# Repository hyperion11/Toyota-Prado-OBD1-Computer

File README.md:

# Toyota-Prado-OBD1-Computer
OBD1 Car computer for Toyota land Cruiser Prado 90 95 1997-2002 5VZ-FE or 3RZ-FE engine

For "Thanks!" you can give me a "coffee" :)

https://www.tinkoff.ru/rm/degtyarev.aleksey35/kHApi80257

or

https://paypal.me/alekseydegtyarev1986?locale.x=ru_RU

BILL OF MATERIALS:

Maple Mini STM32 Dev board http://alii.pub/5snybc

2.4' ILI9341 SPI TFT Screen with flex cable w\o touch http://alii.pub/5snyhd

Capacitors:
22uF 0805 5pcs
http://alii.pub/5snzpw

1uF 0805 2pcs
http://alii.pub/5snzpw

0.1uF 0805 7pcs
http://alii.pub/5snzpw

3.3nF 0805 1pcs
http://alii.pub/5snzpw

100uF 0805 1pcs
http://alii.pub/5snzvc

Diode DO214
http://alii.pub/5so00s

ADC    B4B-ZRROUND           B4B-ZRROUND            B4B-ZR                JST-ZH Connector                                                                                       

BT2                          BATTERY                BATTCOM_20MM_VERTICAL Battery - Single Cell                                                                                 

PTC Fuse 1206 0.7-1A
http://alii.pub/5so034
 
FRAM MB85RC04VPNF 3.3v
http://alii.pub/5so077

LN6206                       MCP1700                SOT23                                                                                                                     LN6206P302MR-G                                                                                                                                                                                                      
Q1     PDTC143XT             MUN2211T1              SC59-BEC              NPN Bias Resistor Transistor                                                                                                                0                                                                                                                                                                           
Q2     PDTA143ZT             MUN2111T1              SC59-BEC              PNP Bias Resistor Transistor                                                                                                                0                                                                                                                                                                           
R1     33K                   R-EU_R0805             R0805                 RESISTOR, European symbol                                                                                                                                                                                                                                                                                               
R3     4                     R-EU_R0805             R0805                 RESISTOR, European symbol                                                                                                                                                                                                                                                                                               
R4     PHOTORESPDV-P9        PHOTORESPDV-P9         PDV-P9XXX             Photoresistor                                                                                                                                                                                                                                                                                                           
R10    20K                   R-EU_R0805             R0805                 RESISTOR, European symbol                                                                                                                                                                                                                                                                                               
R11    6.8K                  R-EU_R0805             R0805                 RESISTOR, European symbol                                                                                                                                                                                                                                                                                               
R12    3.3K                  R-EU_R0805             R0805                 RESISTOR, European symbol                                                                                                                                                                                                                                                                                               
R13    10K                   R-EU_R0805             R0805                 RESISTOR, European symbol                                                                                                                                                                                                                                                                                               
R31    4.7K                  R-EU_R0805             R0805                 RESISTOR, European symbol                                                                                                                                                                                                                                                                                               
R32    4.7K                  R-EU_R0805             R0805                 RESISTOR, European symbol                                                                                                                                                                                                                                                                                               
R38    100                   R-EU_R0805             R0805                 RESISTOR, European symbol                                                                                                                                                                                                                                                                                               
RN1    10K                   RN2_EU-4               CTS-744*083           Chip Resistor Array's from various manufactures                                                     CRA064RJ10K0E04Z                                                                                                                                                                                                    
RN2    2.2K                  RN2_EU-4               CTS-744*083           Chip Resistor Array's from various manufactures                                                     CRA064RJ10K0E04Z                                                                                                                                                                                                    
RN3    10K                   RN2_EU-4               CTS-744*083           Chip Resistor Array's from various manufactures                                                     CRA064RJ10K0E04Z                                                                                                                                                                                                    
RN4    2.2K                  RN2_EU-4               CTS-744*083           Chip Resistor Array's from various manufactures                                                     CRA064RJ10K0E04Z                                                                                                                                                                                                    
S1     DTSM-6                DTSM-6                 DTSM-6                                                                                                                                                                                                                                                                                                                                        
S2     DTSM-6                DTSM-6                 DTSM-6                                                                                                                                                                                                                                                                                                                                        
S3     DTSM-6                DTSM-6                 DTSM-6                                                                                                                                                                                                                                                                                                                                        
S4     DTSM-6                DTSM-6                 DTSM-6                                                                                                                                                                                                                                                                                                                                        
S5     DTSM-6                DTSM-6                 DTSM-6                                                                                                                                                                                                                                                                                                                                        
SERIAL B4B-ZRROUND           B4B-ZRROUND            B4B-ZR                JST-ZH Connector                                                                                                                                                                                                                                                                                                        
SG2    F/QMBIII              F/QMBIII               F/QMBIII              BUZZER Source: Buerklin                                                                                                unknown    unknown   1                                                                                                                                                                                                                                                                                                                          
U$2    JUSHUOAFC08-S18FCA-00 JUSHUOAFC08-S18FCA-00  JUSHUOAFC08-S18FCA-00                                                                                                     AFC08-S18FCA-00                                                                                                                                                                                                     
U$3    main                  B5B-ZRLONG             B5B-ZR-LONG           JST-ZH Connector                                                                                                                                                                                                                                                                                                        
U$4    MINI-DC-DC-3AV        MINI-DC-DC-3AV         MINI-DC-DC-3AV                                                                                                                                                                                                                                                                                                                                
U$5    ADC-4CH-ADS1115       ADC-4CH-ADS1115        ADC-4CH-ADS1115       4 Channel 16-Bit Analog-to-Digital Converter based on ADS1115 chip

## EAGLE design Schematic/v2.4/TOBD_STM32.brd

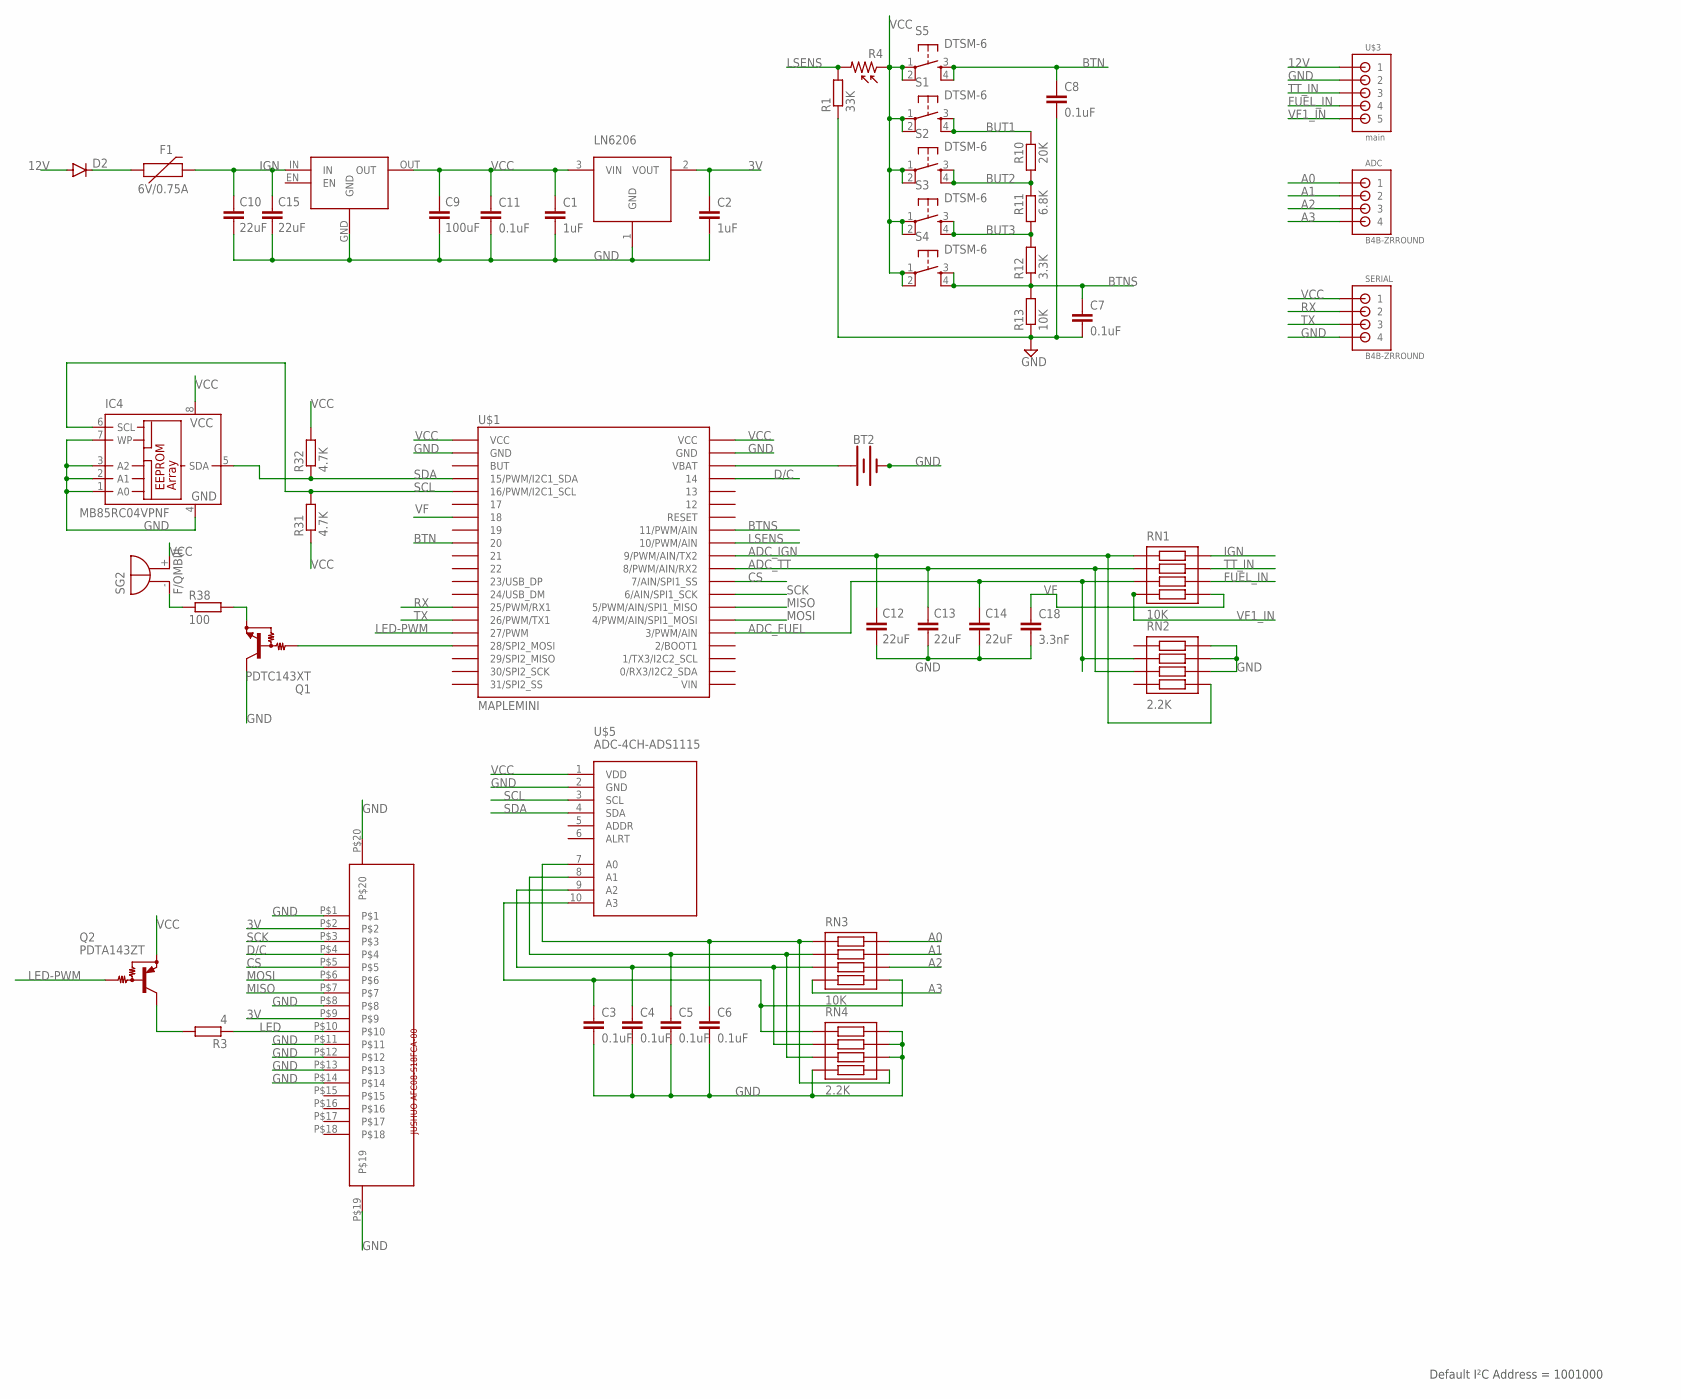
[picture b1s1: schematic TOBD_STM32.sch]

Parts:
ADC: B4B-ZRROUND; B4B-ZR
BT2: BATTERY; BATTCOM_20MM_VERTICAL
C1, C2: 1uF; C0805; MPN CL21F105ZOFNNNE
C3, C4, C5, C6, C7, C8, C11: 0.1uF; C0805; MPN CL21F104ZBCNNNC
C9: 100uF; C1210K; MPN GRM32ER60J107ME20L; LCSC C88154
C10, C12, C13, C14, C15: 22uF; C0805; MPN CL21A226MAQNNNE; LCSC C45783
C18: 3.3nF; C0805; MPN CL21B332KBANNNC
D2: DIODE-DO-214AC; DO-214AC
F1: 6V/0.75A; 1206
IC4: MB85RC04VPNF; SO-08
LN6206: MCP1700; SOT23; MPN LN6206P302MR-G
Q1: PDTC143XT; SC59-BEC
Q2: PDTA143ZT; SC59-BEC
R1: 33K; R0805
R3: 4; R0805
R4: PHOTORESPDV-P9; PDV-P9XXX
R10: 20K; R0805
R11: 6.8K; R0805
R12: 3.3K; R0805
R13: 10K; R0805
R31, R32: 4.7K; R0805
R38: 100; R0805
RN1, RN3: 10K; CTS-744*083; MPN CRA064RJ10K0E04Z
RN2, RN4: 2.2K; CTS-744*083; MPN CRA064RJ10K0E04Z
S1, S2, S3, S4, S5: DTSM-6
SERIAL: B4B-ZRROUND; B4B-ZR
SG2: F/QMBIII
U$1: MAPLEMINI; 20-DIP
U$2: JUSHUOAFC08-S18FCA-00; MPN AFC08-S18FCA-00
U$3: main; B5B-ZR-LONG
U$4: MINI-DC-DC-3AV
U$5: ADC-4CH-ADS1115

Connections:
3V: C2.1, LN6206.2 (VOUT), U$2.P$2, U$2.P$9
12V: D2.A, U$3.1
A0: ADC.1, RN3.5 (8)
A1: ADC.2, RN3.6 (7)
A2: ADC.3, RN3.7 (6)
A3: ADC.4, RN3.8 (4)
ADC_FUEL: C14.1, RN1.2 (3), RN2.3 (2), U$1.25 (3/PWM/AIN)
ADC_IGN: C12.1, RN1.4 (1), RN2.1 (5), U$1.31 (9/PWM/AIN/TX2)
ADC_TT: C13.1, RN1.3 (2), RN2.2 (3), U$1.30 (8/PWM/AIN/RX2)
BTN: C8.1, S5.3, S5.4, U$1.9 (20)
BTNS: C7.1, R12.1, R13.2, S4.3, S4.4, U$1.33 (11/PWM/AIN)
BUT1: R10.2, S1.3, S1.4
BUT2: R10.1, R11.2, S2.3, S2.4
BUT3: R11.1, R12.2, S3.3, S3.4
CS: U$1.29 (7/AIN/SPI1_SS), U$2.P$5
D/C: U$1.37 (14), U$2.P$4
FUEL_IN: RN1.7 (6), U$3.4
GND: BT2.3 (-), C1.2, C2.2, C3.2, C4.2, C5.2, C6.2, C7.2, C8.2, C9.2, C10.2, C11.2, C12.2, C13.2, C14.2, C15.2, C18.2, IC4.1 (A0), IC4.2 (A1), IC4.3 (A2), IC4.4 (GND), IC4.7 (WP), LN6206.1 (GND), Q1.C, R1.1, R13.1, RN2.5 (8), RN2.6 (7), RN2.7 (6), RN4.5 (8), RN4.6 (7), RN4.7 (6), RN4.8 (4), SERIAL.4, U$1.2 (GND), U$1.39 (GND), U$2.P$1, U$2.P$8, U$2.P$11, U$2.P$12, U$2.P$13, U$2.P$14, U$2.P$19, U$2.P$20, U$3.2, U$4.GND, U$5.2 (GND)
IGN: C10.1, C15.1, F1.2, RN1.5 (8), U$4.IN
LED: R3.1, U$2.P$10
LED-PWM: Q2.B, U$1.16 (27/PWM)
LSENS: R1.2, R4.2, U$1.32 (10/PWM/AIN)
MISO: U$1.27 (5/PWM/AIN/SPI1_MISO), U$2.P$7
MOSI: U$1.26 (4/PWM/AIN/SPI1_MOSI), U$2.P$6
unnamed: R38.1, SG2.- (+)
unnamed: Q2.C, R3.2
unnamed: D2.C, F1.1
unnamed: C6.1, RN3.4 (1), RN4.1 (5), U$5.7 (A0)
unnamed: C5.1, RN3.3 (2), RN4.2 (3), U$5.8 (A1)
unnamed: C4.1, RN3.2 (3), RN4.3 (2), U$5.9 (A2)
unnamed: C3.1, RN3.1 (5), RN4.4 (1), U$5.10 (A3)
unnamed: Q1.B, U$1.17 (28/SPI2_MOSI)
unnamed: Q1.E, R38.2
RX: SERIAL.2, U$1.14 (25/PWM/RX1)
SCK: U$1.28 (6/AIN/SPI1_SCK), U$2.P$3
SCL: IC4.6 (SCL), R31.2, U$1.5 (16/PWM/I2C1_SCL), U$5.3 (SCL)
SDA: IC4.5 (SDA), R32.1, U$1.4 (15/PWM/I2C1_SDA), U$5.4 (SDA)
TT_IN: RN1.6 (7), U$3.3
TX: SERIAL.3, U$1.15 (26/PWM/TX1)
VBAT1: BT2.1 (+), BT2.2 (+), U$1.38 (VBAT)
VCC: C1.1, C9.1, C11.1, IC4.8 (VCC), LN6206.3 (VIN), Q2.E, R4.1, R31.1, R32.2, S1.1, S1.2, S2.1, S2.2, S3.1, S3.2, S4.1, S4.2, S5.1, S5.2, SERIAL.1, SG2.+ (-), U$1.1 (VCC), U$1.40 (VCC), U$4.OUT, U$5.1 (VDD)
VF: C18.1, RN1.1 (5), U$1.7 (18)
VF1_IN: RN1.8 (4), U$3.5

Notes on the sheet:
Default I²C Address = 1001000

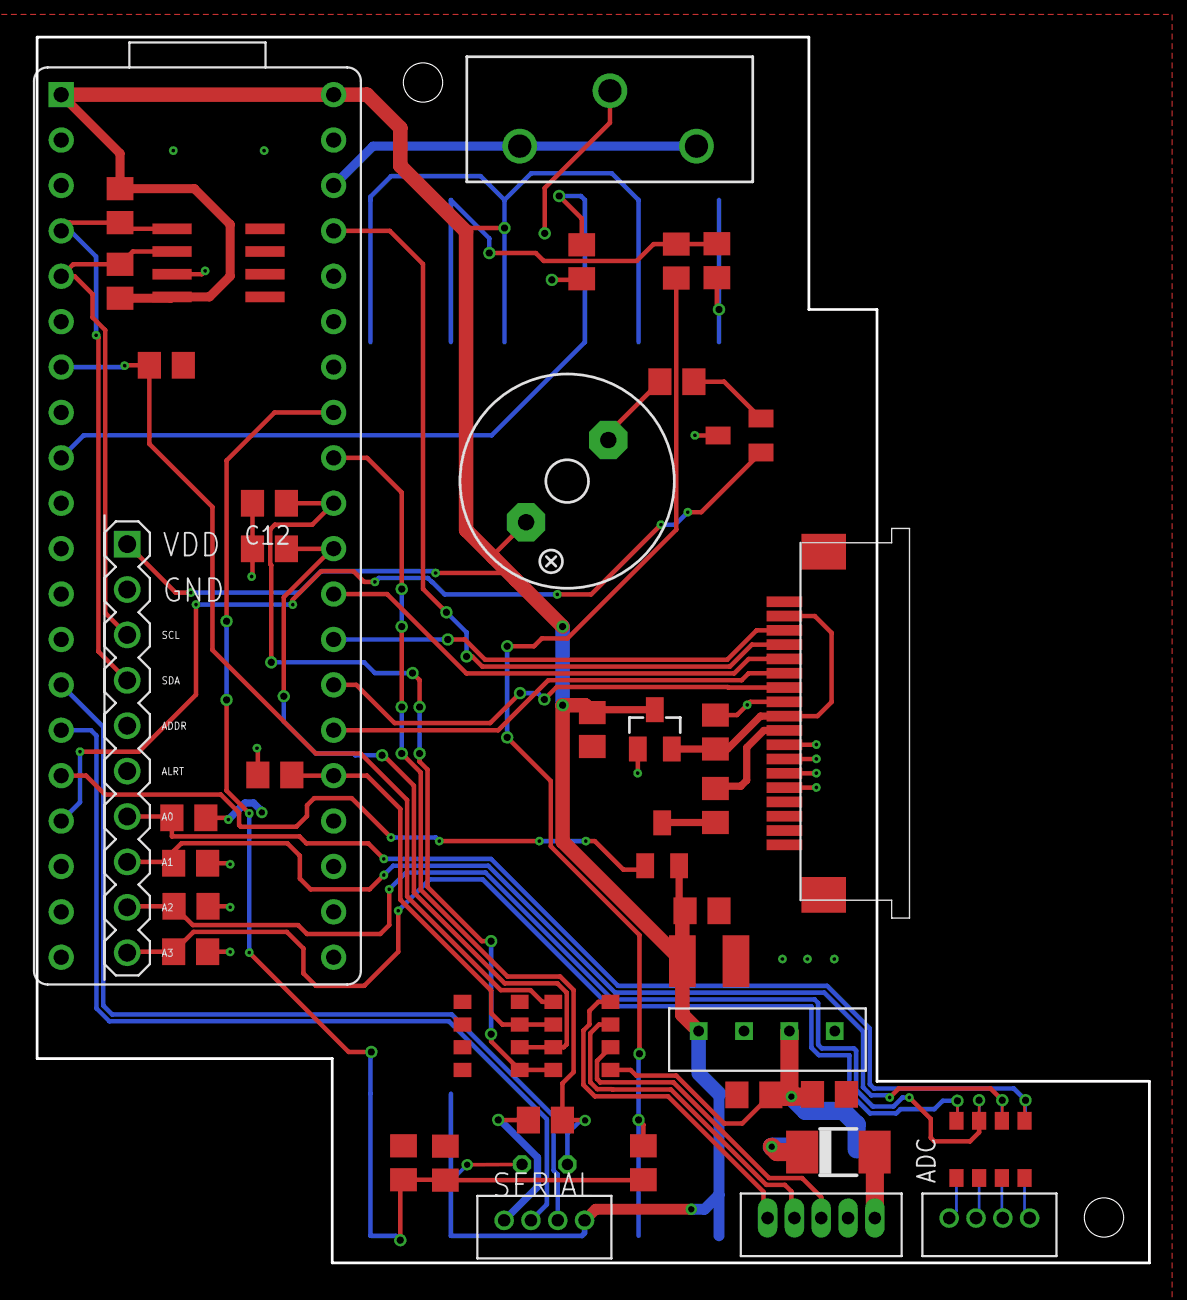
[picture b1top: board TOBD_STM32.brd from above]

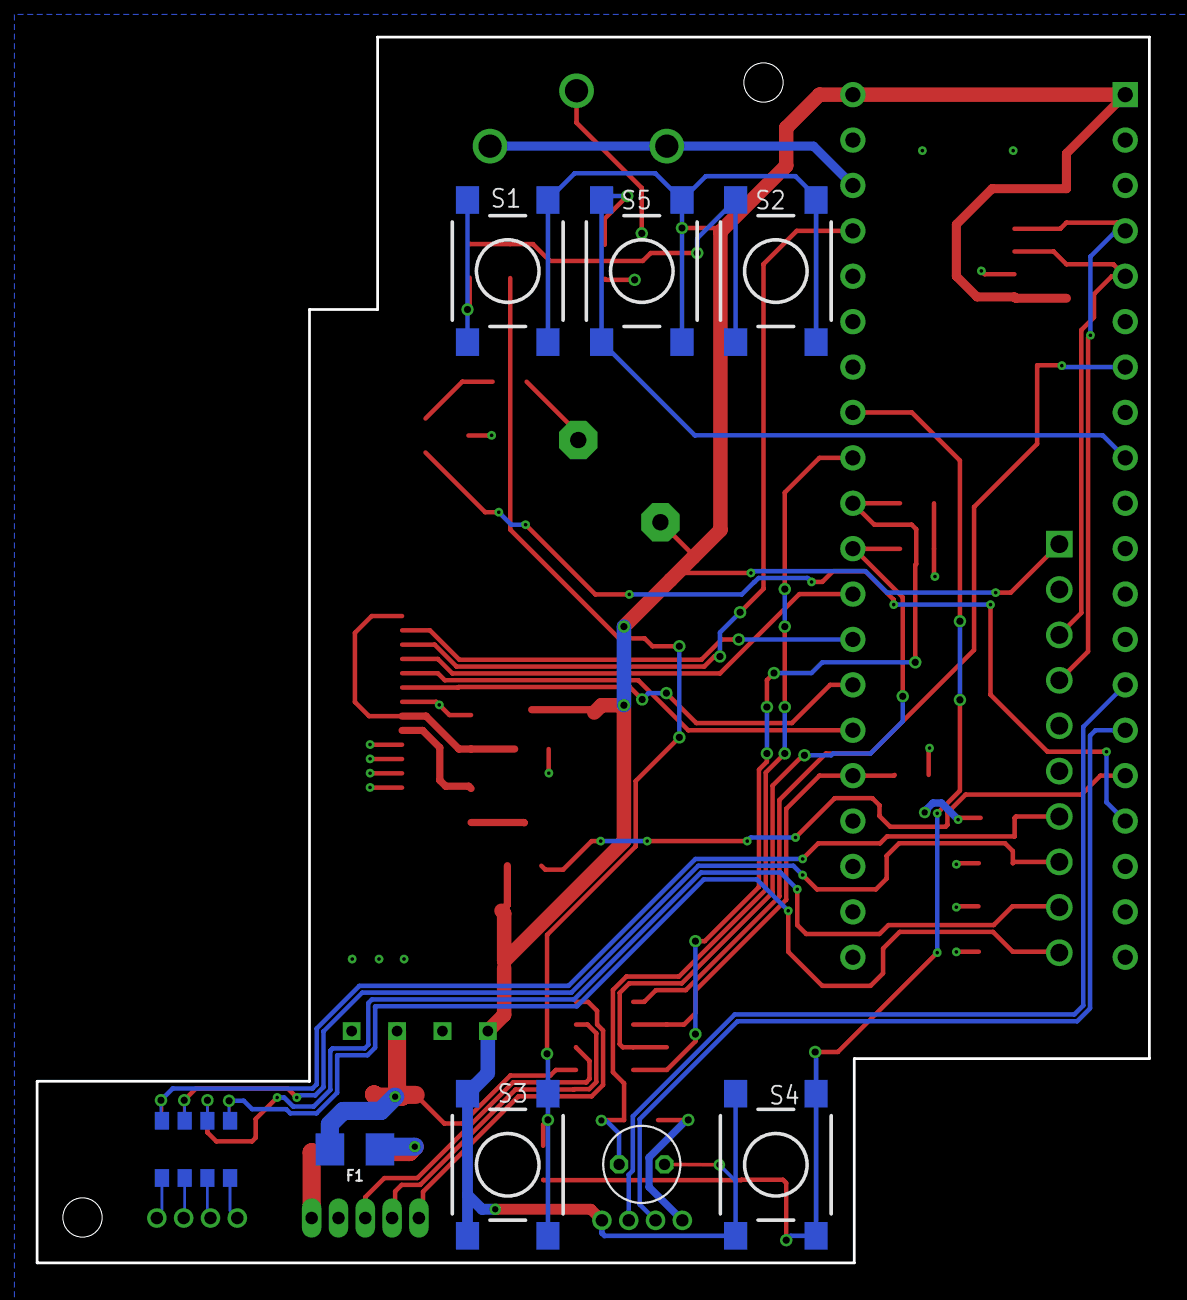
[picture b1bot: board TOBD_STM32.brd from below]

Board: 2 copper layers, 62.2 x 68.6 mm, 50 parts (8 on the bottom side), 43 nets.

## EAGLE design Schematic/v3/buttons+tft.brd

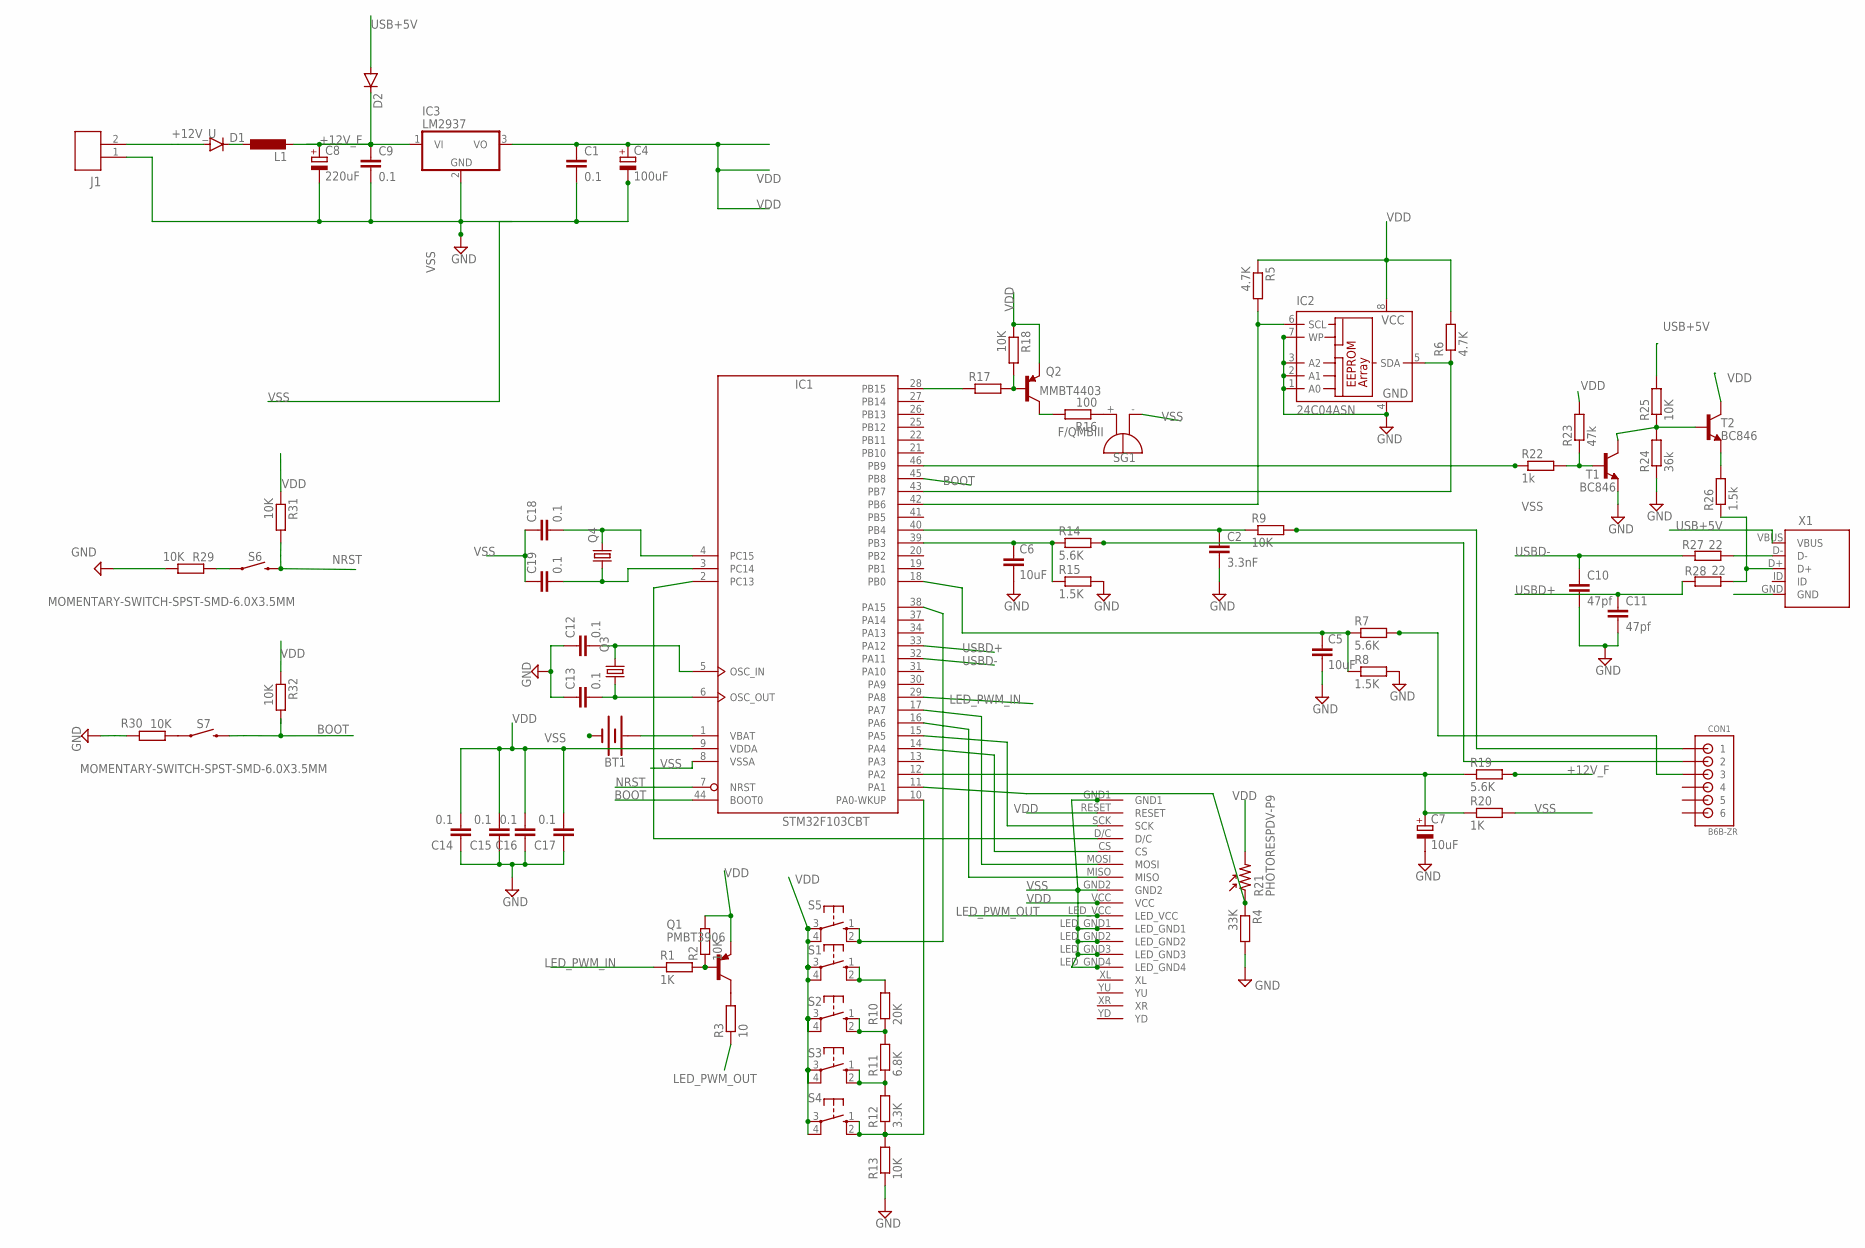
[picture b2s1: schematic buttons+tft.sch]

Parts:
BT1: BATTERY; BATTCOM_20MM_VERTICAL
C1, C9, C12, C13, C14, C15, C16, C17, C18, C19: 0.1; C0805
C2: 3.3nF; C0805
C4: 100uF; SMC_B
C5, C6: 10uF; C0805
C7: 10uF; SMC_A
C8: 220uF; SMC_B
C10, C11: 47pf; C0805
CON1: B6B-ZR
D1, D2: DIODE-SOD123; SOD123
IC1: STM32F103CBT; LQFP48
IC2: 24C04ASN; SO-08
IC3: LM2937; TO263-3
J1: JST_ZH_2PIN
L1: L_EU-CDRH4D28; INDUCTOR_CDRH4
Q1: PMBT3906; SOT23-BEC
Q2: MMBT4403; SOT23-3
Q3: KX-9B; 5.0X3.2_2
Q4: CRYSTALTC26H; TC26H
R1, R17, R20: 1K; R0805
R2, R9, R13, R18, R25, R29, R30, R31, R32: 10K; R0805
R3: 10; R0805
R4: 33K; R0805
R5, R6: 4.7K; R0805
R7, R14, R19: 5.6K; R0805
R8, R15: 1.5K; R0805
R10: 20K; R0805
R11: 6.8K; R0805
R12: 3.3K; R0805
R16: 100; R0805
R21: PHOTORESPDV-P9; PDV-P9XXX
R22: 1k; R0805
R23: 47k; R0805
R24: 36k; R0805
R26: 1.5k; R0805
R27, R28: 22; R0805
S1, S2, S3, S4, S5: 10-XX; B3F-10XX
S6, S7: MOMENTARY-SWITCH-SPST-SMD-6.0X3.5MM; TACTILE_SWITCH_SMD_6.0X3.5MM
SG1: F/QMBIII
T1, T2: BC846; SOT23
U$1: TJC-024-9341
X1: USB-MINI-TH-VERTICAL; USB-MINI_TH-VERTICAL

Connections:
+12V_F: C8.+, C9.1, D2.C, IC3.1 (VI), L1.2, R19.2
+12V_U: D1.A, J1.2
BOOT: IC1.44 (BOOT0), IC1.45 (PB8), R32.2, S7.2
BUT1: R10.2, S1.1 (S), S1.2 (S1)
BUT2: R10.1, R11.2, S2.1 (S), S2.2 (S1)
BUT3: R11.1, R12.2, S3.1 (S), S3.2 (S1)
BUT_PIN: IC1.10 (PA0-WKUP), R12.1, R13.2, S4.1 (S), S4.2 (S1)
FUEL_PIN: CON1.3, R7.2
FUEL_PIN1: C5.1, IC1.18 (PB0), R7.1, R8.1
LED: Q1.C, R3.2
LED_PWM_IN: IC1.29 (PA8), R1.1
LED_PWM_OUT: R3.1, U$1.LED_VCC
unnamed: IC1.38 (PA15), S5.1 (S), S5.2 (S1)
unnamed: IC1.42 (PB6), IC2.6 (SCL), R5.2
unnamed: Q1.B, R1.2, R2.1
unnamed: IC1.17 (PA7), U$1.MOSI
unnamed: IC1.16 (PA6), U$1.MISO
unnamed: IC1.15 (PA5), U$1.SCK
unnamed: IC1.43 (PB7), IC2.5 (SDA), R6.1
unnamed: IC1.14 (PA4), U$1.CS
unnamed: IC1.2 (PC13), U$1.D/C
unnamed: D1.C, L1.1
unnamed: C12.2, IC1.5 (OSC_IN), Q3.2
unnamed: R24.2, R25.1, T1.3 (C), T2.1 (B)
unnamed: IC1.28 (PB15), R17.1
unnamed: R22.2, R23.1, T1.1 (B)
unnamed: Q2.1 (B), R17.2, R18.2
unnamed: Q2.3 (C), R16.2
unnamed: R16.1, SG1.+ (-)
unnamed: C13.2, IC1.6 (OSC_OUT), Q3.1
unnamed: R26.2, T2.2 (E)
unnamed: R29.1, S6.1
unnamed: C7.+, IC1.12 (PA2), R19.1, R20.1
unnamed: R26.1, R28.1, X1.D+
unnamed: R27.1, X1.D-
unnamed: C18.2, IC1.4 (PC15), Q4.2
unnamed: C19.2, IC1.3 (PC14), Q4.1
unnamed: R30.1, S7.1
unnamed: IC1.46 (PB9), R22.1
NRST: IC1.7 (NRST), R31.2, S6.2
PHOTORE_PIN: IC1.11 (PA1), R4.1, R21.1
TT_PIN1: CON1.2, R14.2
TT_PIN_2: C6.1, IC1.39 (PB3), R14.1, R15.1
USB+5V: D2.A, R25.2, X1.VBUS
USBD+: C11.1, IC1.33 (PA12), R28.2
USBD-: C10.1, IC1.32 (PA11), R27.2
VBAT1: BT1.1 (+), BT1.2 (+), IC1.1 (VBAT)
VDD: C1.1, C4.+, C14.2, C15.2, C16.2, C17.2, IC1.9 (VDDA), IC1.24 (VDD), IC1.36 (VDD), IC1.48 (VDD), IC2.8 (VCC), IC3.3 (VO), Q1.E, Q2.2 (E), R2.2, R5.1, R6.2, R18.1, R21.2, R23.2, R31.1, R32.1, S1.3, S1.4 (P1), S2.3, S2.4 (P1), S3.3, S3.4 (P1), S4.3, S4.4 (P1), S5.3, S5.4 (P1), T2.3 (C), U$1.RESET, U$1.VCC
VF_PIN: C2.1, IC1.40 (PB4), R9.1
VF_PIN1: CON1.1, R9.2
VSS: BT1.3 (-), C1.2, C2.2, C4.-, C5.2, C6.2, C7.-, C8.-, C9.2, C10.2, C11.2, C12.1, C13.1, C14.1, C15.1, C16.1, C17.1, C18.1, C19.1, IC1.8 (VSSA), IC1.23 (VSS), IC1.35 (VSS), IC1.47 (VSS), IC2.1 (A0), IC2.2 (A1), IC2.3 (A2), IC2.4 (GND), IC2.7 (WP), IC3.2 (GND), J1.1, R4.2, R8.2, R13.1, R15.2, R20.2, R24.1, R29.2, R30.2, SG1.- (+), T1.2 (E), U$1.GND1, U$1.GND2, U$1.LED_GND1, U$1.LED_GND2, U$1.LED_GND3, U$1.LED_GND4, X1.GND

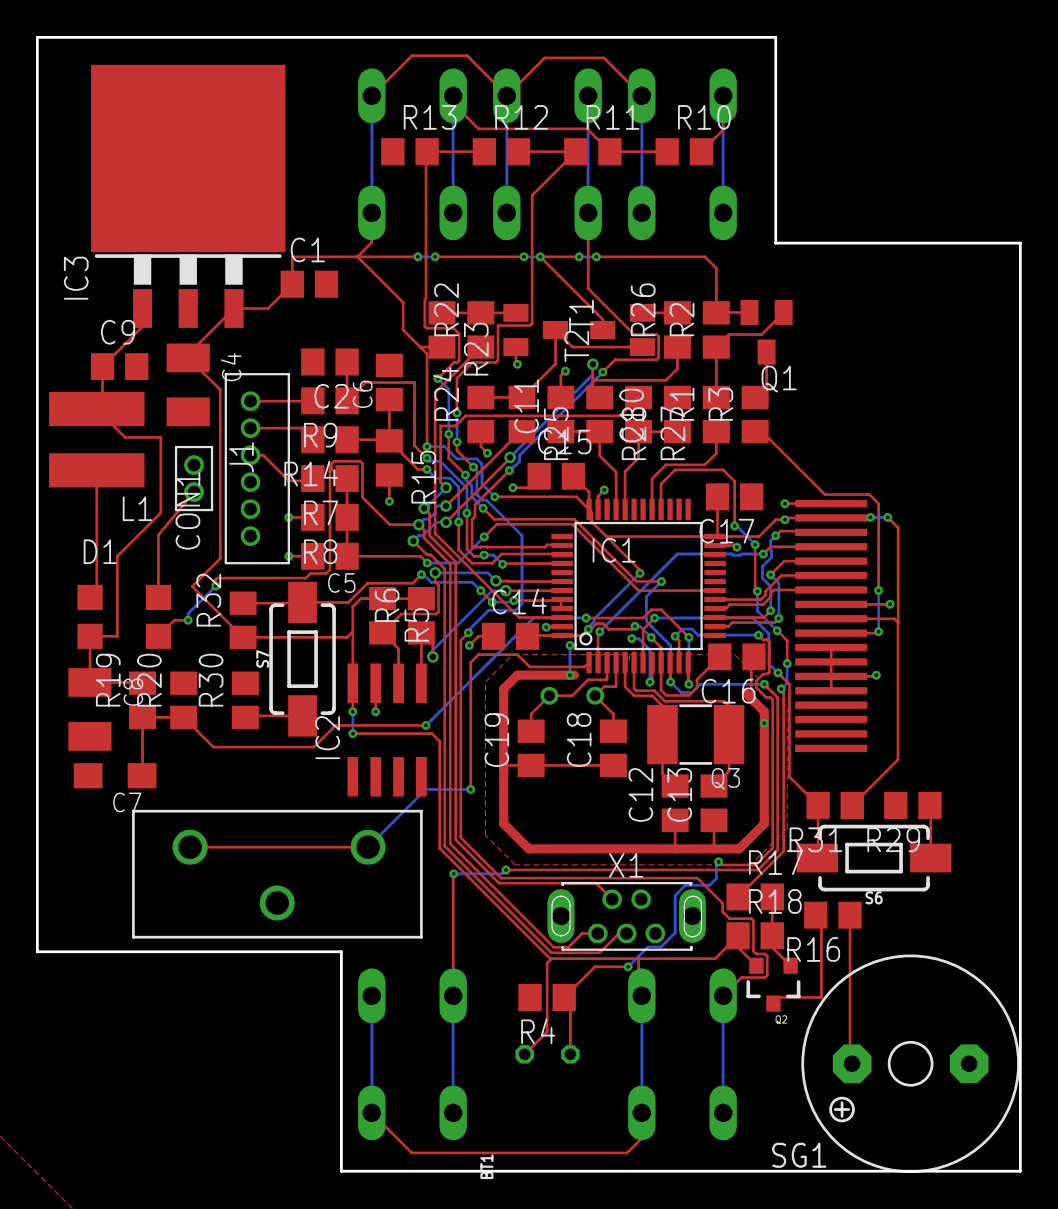
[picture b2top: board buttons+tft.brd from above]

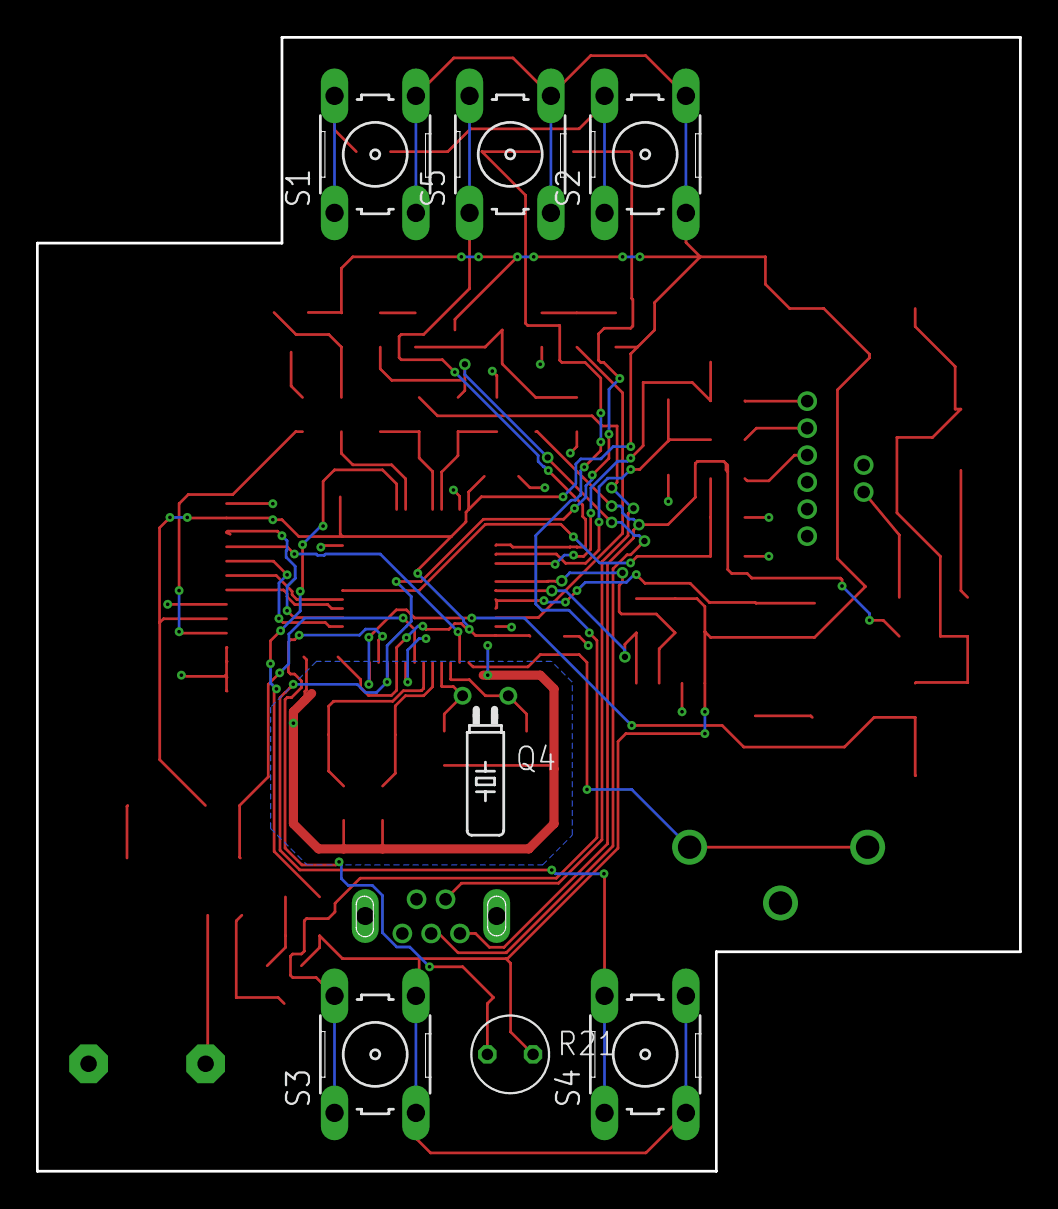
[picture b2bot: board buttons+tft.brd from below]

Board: 2 copper layers, 54.6 x 63.0 mm, 75 parts (7 on the bottom side), 51 nets.

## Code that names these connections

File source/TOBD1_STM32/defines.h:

#ifndef DEFINES_H
#define DEFINES_H

#define VREF_MEASURED 3.32              //Измеренное опорное напряжение с 3.3В стабилизатора

#if (HW_VERSION==2)
#define TT_PIN_DIVIDER 2.87
#elif (HW_VERSION==3)
#define TT_PIN_DIVIDER 4.73
#endif

#if defined (ADS1115)
#define ADS1115_A0_A1_DIVIDER 2
#define ADS1115_A2_A3_DIVIDER 4.73
#endif

#define FUEL_PIN_DIVIDER 4.73
#define VCC_PIN_DIVIDER 6.6
#define interval2 2                      //2ms Интервал
#define interval500 500
//#define SECOND_O2SENS  // Включение 2го сенсора кислорода для V движков
#define DEBUG_OUTPUT false // for debug option - swith output to Serial
//DEFINE пинов под входы-выходы
//ADC PIN's  3, 4, 5, 6, 7, 8, 9, 10, 11
//#define LED_PIN         33  //встроенный светодиод
#define FUEL_PIN           PB0  //D3-для датчика уровня топлива
#define TT_PIN             PA3  //D8-PA3 для сенсора ТТ АКПП
#define ENGINE_DATA_PIN    PB4  //D18-PB5-EXTI5 VF1 PIN
#define TFT_CS             PA4  //D7   //SS
#define TFT_DC             PC13 //D14
#define TFT_LED_PIN        PA8  //27 -PA2 для шим подсветки дисплея
#define LIGHT_SENSOR_PIN   PA1  //D10-PA1 Для фоторезистора
#define BUTTON_ARRAY_PIN   PA0  //D11-PA0 для массива из 4х кнопок
#define RESET_PIN          PA15  //D20 отдельно для кнопки сброса //2.1
#define VCC_PIN            PA2 //D9 сенсор напряжения 12В
#define VCC_DROP           112 //падение напряжения на диоде 0.6v/6.6/3.32

//DEFINE констант расходомера
#if defined(VZ)
#define Ncyl 6.0      //6 форсунок
#elif defined(RZ)
#define Ncyl 4.0        //4 форсунки
#else
#error “Unsupported Engine!!!”
#endif

#define FuelCapacity 90
//DEFINE OBD READER
#define  MY_HIGH  HIGH //LOW    // I have inverted the Eng line using an Opto-Coupler, if yours isn't then reverse these low & high defines.
#define  MY_LOW   LOW //HIGH
#define  TOYOTA_MAX_BYTES  24
#define OBD_INJ 0 //Injector pulse width (INJ)
#define OBD_IGN 1 //Ignition timing angle (IGN)
#define OBD_IAC 2 //Idle Air Control (IAC)
#define OBD_RPM 3 //Engine speed (RPM)
#define OBD_MAP 4 //Manifold Absolute Pressure (MAP)
#define OBD_ECT 5 //Engine Coolant Temperature (ECT)
#define OBD_TPS 6 // Throttle Position Sensor (TPS)
#define OBD_SPD 7 //Speed (SPD)
#define OBD_OXSENS 8 // Oxygen sensor 1

#ifdef SECOND_O2SENS    // Oxygen sensor 2
#define TOBD_ID_MAX 10
#define OBD_OXSENS2 9
const char* TOBD_ID_NAME[TOBD_ID_MAX] = {"INJ", "IGN", "IAC", "RPM", "MAF", "ECT", "TPS", "SPD", "VF1", "VF2"};
#else
#define TOBD_ID_MAX 9
const char* TOBD_ID_NAME[TOBD_ID_MAX] = {"INJ", "IGN", "IAC", "RPM", "MAF", "ECT", "TPS", "SPD", "VF"};
#endif

#define ILI9341_GREY 0x8410
#endif

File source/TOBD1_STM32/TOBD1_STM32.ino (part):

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  FRAM.begin();
  pinMode(ENGINE_DATA_PIN, INPUT); // VF1 PIN
  pinMode(TT_PIN, INPUT_ANALOG);
  pinMode(FUEL_PIN, INPUT_ANALOG);
  pinMode(VCC_PIN, INPUT_ANALOG);
  pinMode(BUTTON_ARRAY_PIN, INPUT_ANALOG);
  pinMode(TFT_LED_PIN, PWM);
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  writeHeader();
  isActive = false;
  ADC.index = 0;
  ADC.tt_in = 0;
  ADC.fuel_in = 0;
  ADC.vcc_in = 0;
  init_ = false;
#if defined(DEBUG_SERIAL_OUTPUT)
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    if (ADC.index < 20)
    {
      ADC.vcc_in += analogRead(VCC_PIN) + VCC_DROP;
      ADC.fuel_in += analogRead(FUEL_PIN);
      ADC.index++;
    }
    if (ADC.tt_index < 100) {
      ADC.tt_in += analogRead(TT_PIN);
      ADC.tt_index++;
    }
    else ADC.is_ready = true;
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      TT.last = TT.current;
    }
    ADC.tt_index = 0;
    ADC.tt_in = 0;
    ADC.is_ready = false;
  }
  if ((ToyotaNumBytes > 0) && (CurrentDisplayIDX != 4))  {  // if found bytes
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      fuel.remains -= cycle_obd_inj_dur * Ls / 1000.0; //остаток в баке стал децл меньше
      t = new_t;//тест
      ADC.fuel_avg = ADC.fuel_in / ADC.index;
      fuel.volt = (float)analogRead(FUEL_PIN) * VREF_MEASURED * FUEL_PIN_DIVIDER / 4095.0;
      fuel.volt_avg = (float)ADC.fuel_avg * VREF_MEASURED * FUEL_PIN_DIVIDER / 4095.0;
      ADC.vcc_avg = ADC.vcc_in / ADC.index;
      logData();
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    for (uint8_t i = 0; i < TOBD_ID_MAX + 1; i++)
      OLDOBDFLAG[i] = OBDFLAG[i];
    ToyotaNumBytes = 0;     // reset the counter.
    ADC.fuel_in = 0;
    ADC.vcc_in = 0;
    ADC.index = 0;
  } // end if (ToyotaNumBytes > 0)
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
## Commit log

2021-05-25 added source codes

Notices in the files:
parts and their libraries:
SparkFun-Batteries: Licensing: Creative Commons ShareAlike 4.0 International - https://creativecommons.org/licenses/by-sa/4.0
m-pad-2.1: License : GNU General Public License version 2 (see bottom)
crystal-geyer_V1_0: Copyright: Geyer-Electronic
